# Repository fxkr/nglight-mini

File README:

nglight-mini r0
===============

What is it?

    A tiny, I2C-controlled 6-channel low-side PWM LED driver based on the PCA9685.
    Just a smaller version of this: http://ng.uavp.ch/moin/Documentation/NGlight

Part list:

    See parts.csv

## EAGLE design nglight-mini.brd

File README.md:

# nglight-mini r0

## What is it?

A tiny, I2C-controlled 6-channel low-side PWM LED driver based on the PCA9685.
It's just a smaller version of this: http://ng.uavp.ch/moin/Documentation/NGlight

Both schematic and layout are proven.

## Part list?

See parts.csv

## Images

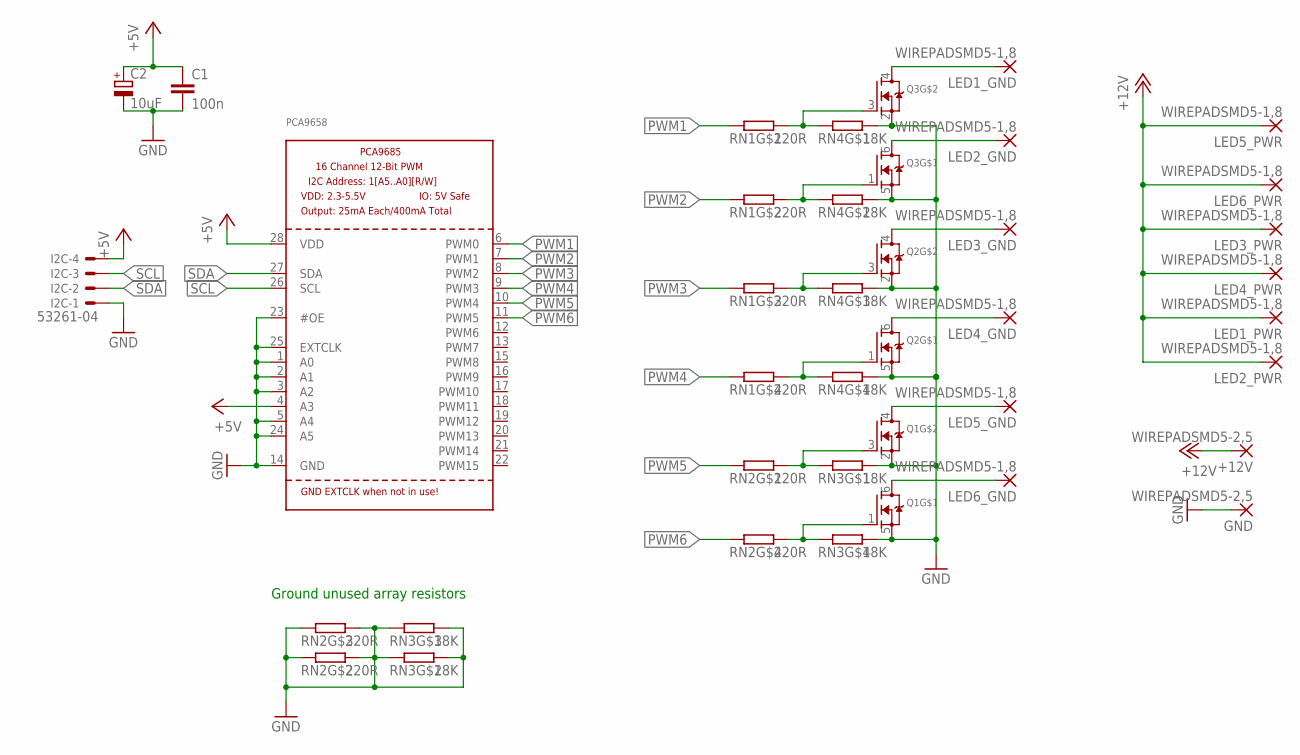
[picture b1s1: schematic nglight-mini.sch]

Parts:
+12V: WIREPADSMD5-2,5; 5-2,5
C1: 100n; C0805
C2: 10uF; UD-5X5,8_NICHICON
GND: WIREPADSMD5-2,5; 5-2,5
I2C: 53261-04
LED1_GND, LED1_PWR, LED2_GND, LED2_PWR, LED3_GND, LED3_PWR, LED4_GND, LED4_PWR, LED5_GND, LED5_PWR, LED6_GND, LED6_PWR: WIREPADSMD5-1,8; 5-1,8
PCA9658: PCA9685; TSSOP28
Q1, Q2, Q3: MOSFET-N; SOT23-6
RN1, RN2: 220R; 0603_ARRAY_4
RN3, RN4: 18K; 0603_ARRAY_4

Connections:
+5V: C1.1, C2.+, I2C.4, PCA9658.4 (A3), PCA9658.28 (VDD)
+12V: +12V.1, LED1_PWR.1, LED2_PWR.1, LED3_PWR.1, LED4_PWR.1, LED5_PWR.1, LED6_PWR.1
GND: C1.2, C2.-, GND.1, I2C.1, PCA9658.1 (A0), PCA9658.2 (A1), PCA9658.3 (A2), PCA9658.5 (A4), PCA9658.14 (GND), PCA9658.23 (#OE), PCA9658.24 (A5), PCA9658.25 (EXTCLK), Q1.2 (S), Q1.5 (S), Q2.2 (S), Q2.5 (S), Q3.2 (S), Q3.5 (S), RN2.2, RN2.3, RN2.6, RN2.7, RN3.2, RN3.3, RN3.5, RN3.6, RN3.7, RN3.8, RN4.5, RN4.6, RN4.7, RN4.8
LED1: LED1_GND.1, Q3.4 (D)
LED2: LED2_GND.1, Q3.6 (D)
LED3: LED3_GND.1, Q2.4 (D)
LED4: LED4_GND.1, Q2.6 (D)
LED5: LED5_GND.1, Q1.4 (D)
unnamed: LED6_GND.1, Q1.6 (D)
unnamed: Q1.3 (G), RN2.8, RN3.1
unnamed: Q1.1 (G), RN2.5, RN3.4
unnamed: Q2.3 (G), RN1.6, RN4.3
unnamed: Q2.1 (G), RN1.5, RN4.4
unnamed: Q3.3 (G), RN1.8, RN4.1
unnamed: Q3.1 (G), RN1.7, RN4.2
PWM1: PCA9658.6 (PWM0), RN1.1
PWM2: PCA9658.7 (PWM1), RN1.2
PWM3: PCA9658.8 (PWM2), RN1.3
PWM4: PCA9658.9 (PWM3), RN1.4
PWM5: PCA9658.10 (PWM4), RN2.1
PWM6: PCA9658.11 (PWM5), RN2.4
SCL: I2C.3, PCA9658.26 (SCL)
SDA: I2C.2, PCA9658.27 (SDA)

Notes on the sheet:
Ground unused array resistors

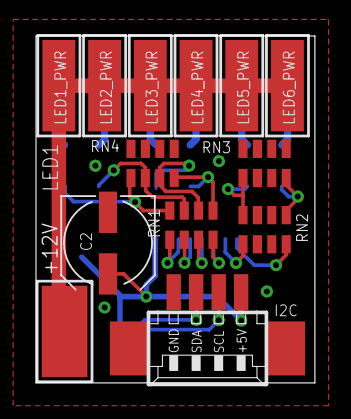
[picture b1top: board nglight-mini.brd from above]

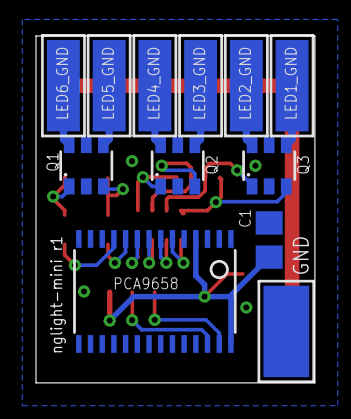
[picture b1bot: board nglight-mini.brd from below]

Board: 2 copper layers, 15.5 x 19.3 mm, 25 parts (12 on the bottom side), 23 nets.

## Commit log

2013-08-22 Add .gitignore
2013-08-22 Import adafruit library (public domain)
    Source:
    https://github.com/adafruit/Adafruit-Eagle-Library
2013-08-22 Add dual mosfet library
    Part/symbol copied from adafruit library
2013-08-22 Add oshpark design rules
    http://oshpark.com/guidelines
2013-08-22 Add nglight-mini sch/brd
2013-08-23 Minor changes
2013-08-23 Add README and (yet incomplete) parts.csv
2013-09-22 Ground unused array resistors
2013-10-04 Rev 1; various small improvements, incl.:
    - bigger traces (6 mil -> 10 mil)
    - larger footprint for the big cap
    - remove a small piece of trace between two pins
    that wasn't supposed to be there
2013-10-07 Major changes in layout
    The resistor arrays proved hard to solder, so I increased
    the pad size. Due to the tight space constraints, this led
    to relatively big changes in the board. One consequence is
    that traces are now 8mil - a compromise between the 6mil
    that seemed too fine and the 10mil that just wont fit.
2013-10-08 Cosmetics
2013-10-08 Minor trace/via adjustments
2013-10-08 Use vector font for all texts
    The fab will use vector fonts either way and due to the size
    difference between the proportional and the vector font they'd
    come out all wrong. Oops.
2013-10-08 Minor fix (via was very close too pad)
2015-05-01 README: markdown, images
2015-05-01 Add screenshots
